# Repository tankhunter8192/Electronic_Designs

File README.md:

# Electronic_Designs
 Collection of Electronic Scemetics and PCB Designs

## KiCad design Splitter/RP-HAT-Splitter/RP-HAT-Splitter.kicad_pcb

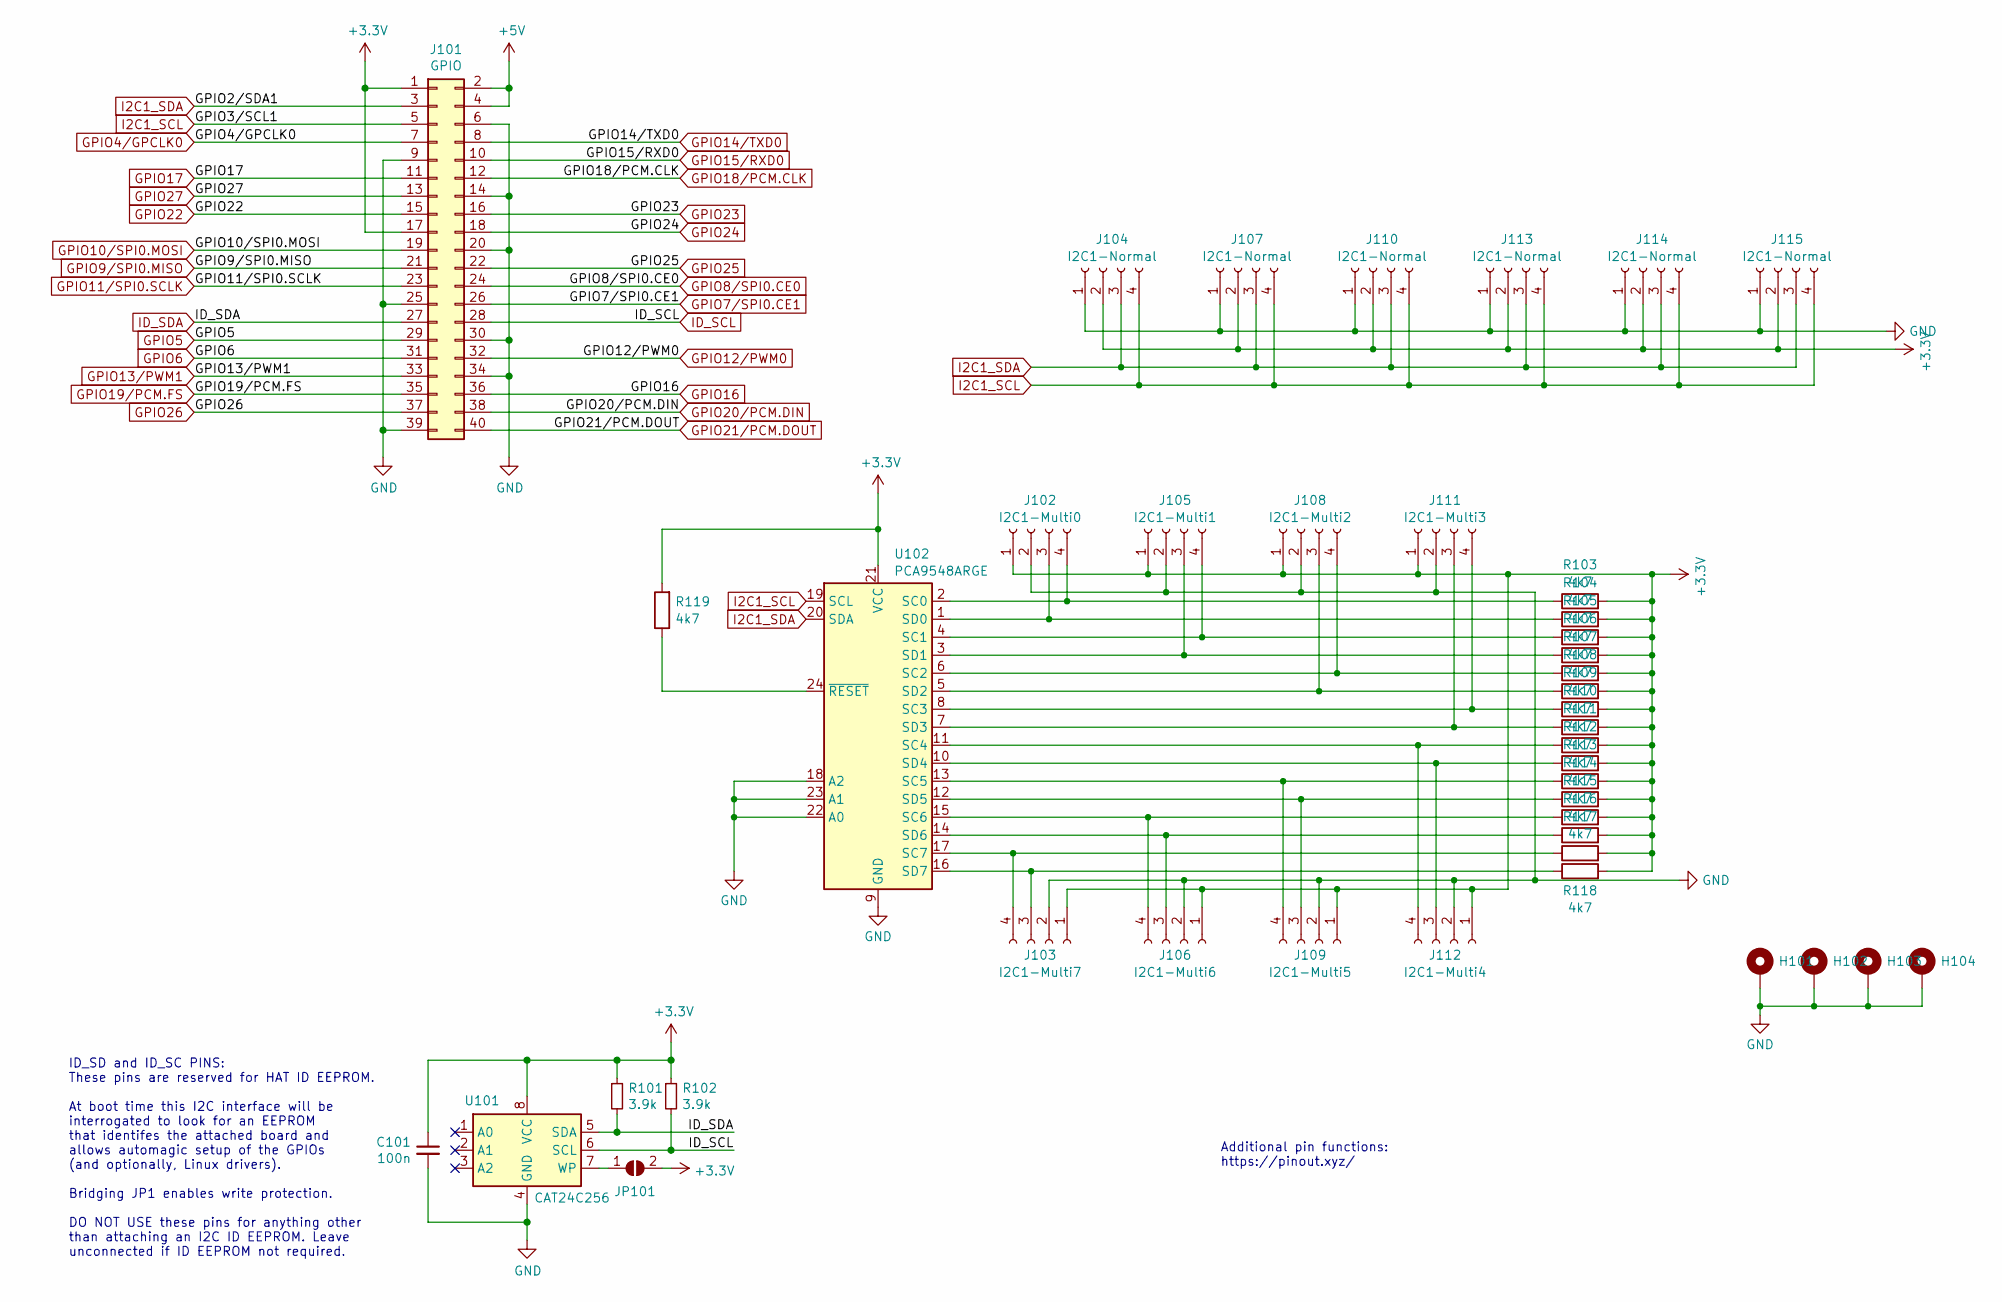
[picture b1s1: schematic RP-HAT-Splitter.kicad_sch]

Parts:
C101: 100n
H101, H102, H103, H104: MountingHole_Pad; MountingHole_3.2mm_M3_DIN965_Pad_TopBottom
J101: GPIO; PinSocket_2x20_P2.54mm_Vertical
J102: I2C1-Multi0; JST_SH_SM04B-SRSS-TB_1x04-1MP_P1.00mm_Horizontal
J103: I2C1-Multi7; JST_SH_SM04B-SRSS-TB_1x04-1MP_P1.00mm_Horizontal
J104, J107, J110, J113, J114, J115: I2C1-Normal; JST_SH_BM04B-SRSS-TB_1x04-1MP_P1.00mm_Vertical
J105: I2C1-Multi1; JST_SH_SM04B-SRSS-TB_1x04-1MP_P1.00mm_Horizontal
J106: I2C1-Multi6; JST_SH_SM04B-SRSS-TB_1x04-1MP_P1.00mm_Horizontal
J108: I2C1-Multi2; JST_SH_SM04B-SRSS-TB_1x04-1MP_P1.00mm_Horizontal
J109: I2C1-Multi5; JST_SH_SM04B-SRSS-TB_1x04-1MP_P1.00mm_Horizontal
J111: I2C1-Multi3; JST_SH_SM04B-SRSS-TB_1x04-1MP_P1.00mm_Horizontal
J112: I2C1-Multi4; JST_SH_SM04B-SRSS-TB_1x04-1MP_P1.00mm_Horizontal
JP101: ID_WP; SolderJumper-3_P2.0mm_Open_TrianglePad1.0x1.5mm_NumberLabels
R101, R102: 3.9k; R_0612_1632Metric_Pad1.18x3.40mm_HandSolder
R103, R104, R105, R106, R107, R108, R109, R110, R111, R112, R113, R114, R115, R116, R117, R118, R119: 4k7; R_1206_3216Metric_Pad1.30x1.75mm_HandSolder
U101: CAT24C256; SOIC127P600X175-8M
U102: PCA9548ARGE; Texas_RGE0024C_EP2.1x2.1mm

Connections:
+3V3: C101.1, J101.1, J101.17, J102.1, J103.1, J104.2, J105.1, J106.1, J107.2, J108.1, J109.1, J110.2, J111.1, J112.1, J113.2, J114.2, J115.2, JP101.2 (B), R101.1, R102.1, R103.2, R104.2, R105.2, R106.2, R107.2, R108.2, R109.2, R110.2, R111.2, R112.2, R113.2, R114.2, R115.2, R116.2, R117.2, R118.2, R119.2, U101.8 (VCC), U102.21 (VCC)
+5V: J101.2, J101.4
GND: C101.2, H101.1, H102.1, H103.1, H104.1, J101.6, J101.9, J101.14, J101.20, J101.25, J101.30, J101.34, J101.39, J102.2, J103.2, J103.MP, J104.1, J104.MP, J105.2, J105.MP, J106.2, J106.MP, J107.1, J107.MP, J108.2, J108.MP, J109.2, J109.MP, J110.1, J110.MP, J111.2, J111.MP, J112.2, J112.MP, J113.1, J113.MP, J114.1, J114.MP, J115.1, J115.MP, U101.4 (GND), U102.9 (GND), U102.18 (A2), U102.22 (A0), U102.23 (A1)
GPIO4/GPCLK0: J101.7
GPIO5: J101.29
GPIO6: J101.31
GPIO7/SPI0.CE1: J101.26
GPIO8/SPI0.CE0: J101.24
GPIO9/SPI0.MISO: J101.21
GPIO10/SPI0.MOSI: J101.19
GPIO11/SPI0.SCLK: J101.23
GPIO12/PWM0: J101.32
GPIO13/PWM1: J101.33
GPIO14/TXD0: J101.8
GPIO15/RXD0: J101.10
GPIO16: J101.36
GPIO17: J101.11
GPIO18/PCM.CLK: J101.12
GPIO19/PCM.FS: J101.35
GPIO20/PCM.DIN: J101.38
GPIO21/PCM.DOUT: J101.40
GPIO22: J101.15
GPIO23: J101.16
GPIO24: J101.18
GPIO25: J101.22
GPIO26: J101.37
GPIO27: J101.13
I2C1_SCL: J101.5, J104.4, J107.4, J110.4, J113.4, J114.4, J115.4, U102.19 (SCL)
I2C1_SDA: J101.3, J104.3, J107.3, J110.3, J113.3, J114.3, J115.3, U102.20 (SDA)
ID_SCL: J101.28, R102.2, U101.6 (SCL)
ID_SDA: J101.27, R101.2, U101.5 (SDA)
unnamed: J102.3, R104.1, U102.1 (SD0)
unnamed: J102.4, R103.1, U102.2 (SC0)
unnamed: J103.3, R118.1, U102.16 (SD7)
unnamed: J103.4, R117.1, U102.17 (SC7)
unnamed: J105.3, R106.1, U102.3 (SD1)
unnamed: J105.4, R105.1, U102.4 (SC1)
unnamed: J106.3, R116.1, U102.14 (SD6)
unnamed: J106.4, R115.1, U102.15 (SC6)
unnamed: J108.3, R108.1, U102.5 (SD2)
unnamed: J108.4, R107.1, U102.6 (SC2)
unnamed: J109.3, R114.1, U102.12 (SD5)
unnamed: J109.4, R113.1, U102.13 (SC5)
unnamed: J111.3, R110.1, U102.7 (SD3)
unnamed: J111.4, R109.1, U102.8 (SC3)
unnamed: J112.3, R112.1, U102.10 (SD4)
unnamed: J112.4, R111.1, U102.11 (SC4)
unnamed: JP101.1 (A), U101.7 (WP)
unnamed: R119.1, U102.24 (~RESET)

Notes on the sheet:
Additional pin functions: https://pinout.xyz/
ID_SD and ID_SC PINS: These pins are reserved for HAT ID EEPROM. At boot time this I2C interface will be interrogated to look for an EEPROM that identifes the attached board and allows automagic setup of the GPIOs (and optionally, Linux drivers). Bridging JP1 enables write protection. DO NOT USE th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

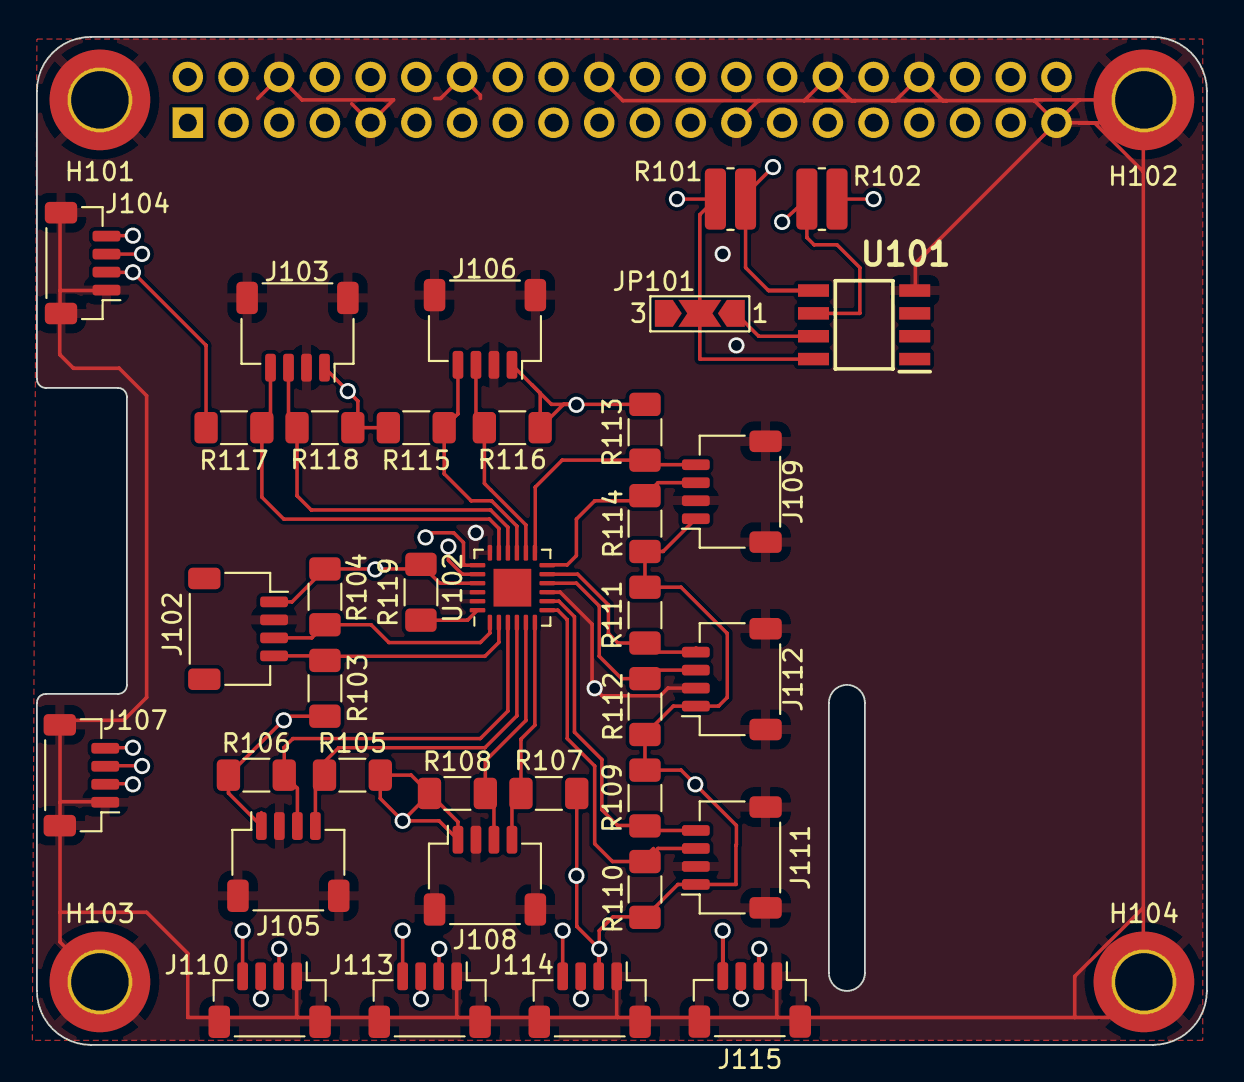
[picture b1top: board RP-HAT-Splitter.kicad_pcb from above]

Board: 4 copper layers, 65.0 x 56.0 mm, 41 parts (1 on the bottom side), 25 nets.

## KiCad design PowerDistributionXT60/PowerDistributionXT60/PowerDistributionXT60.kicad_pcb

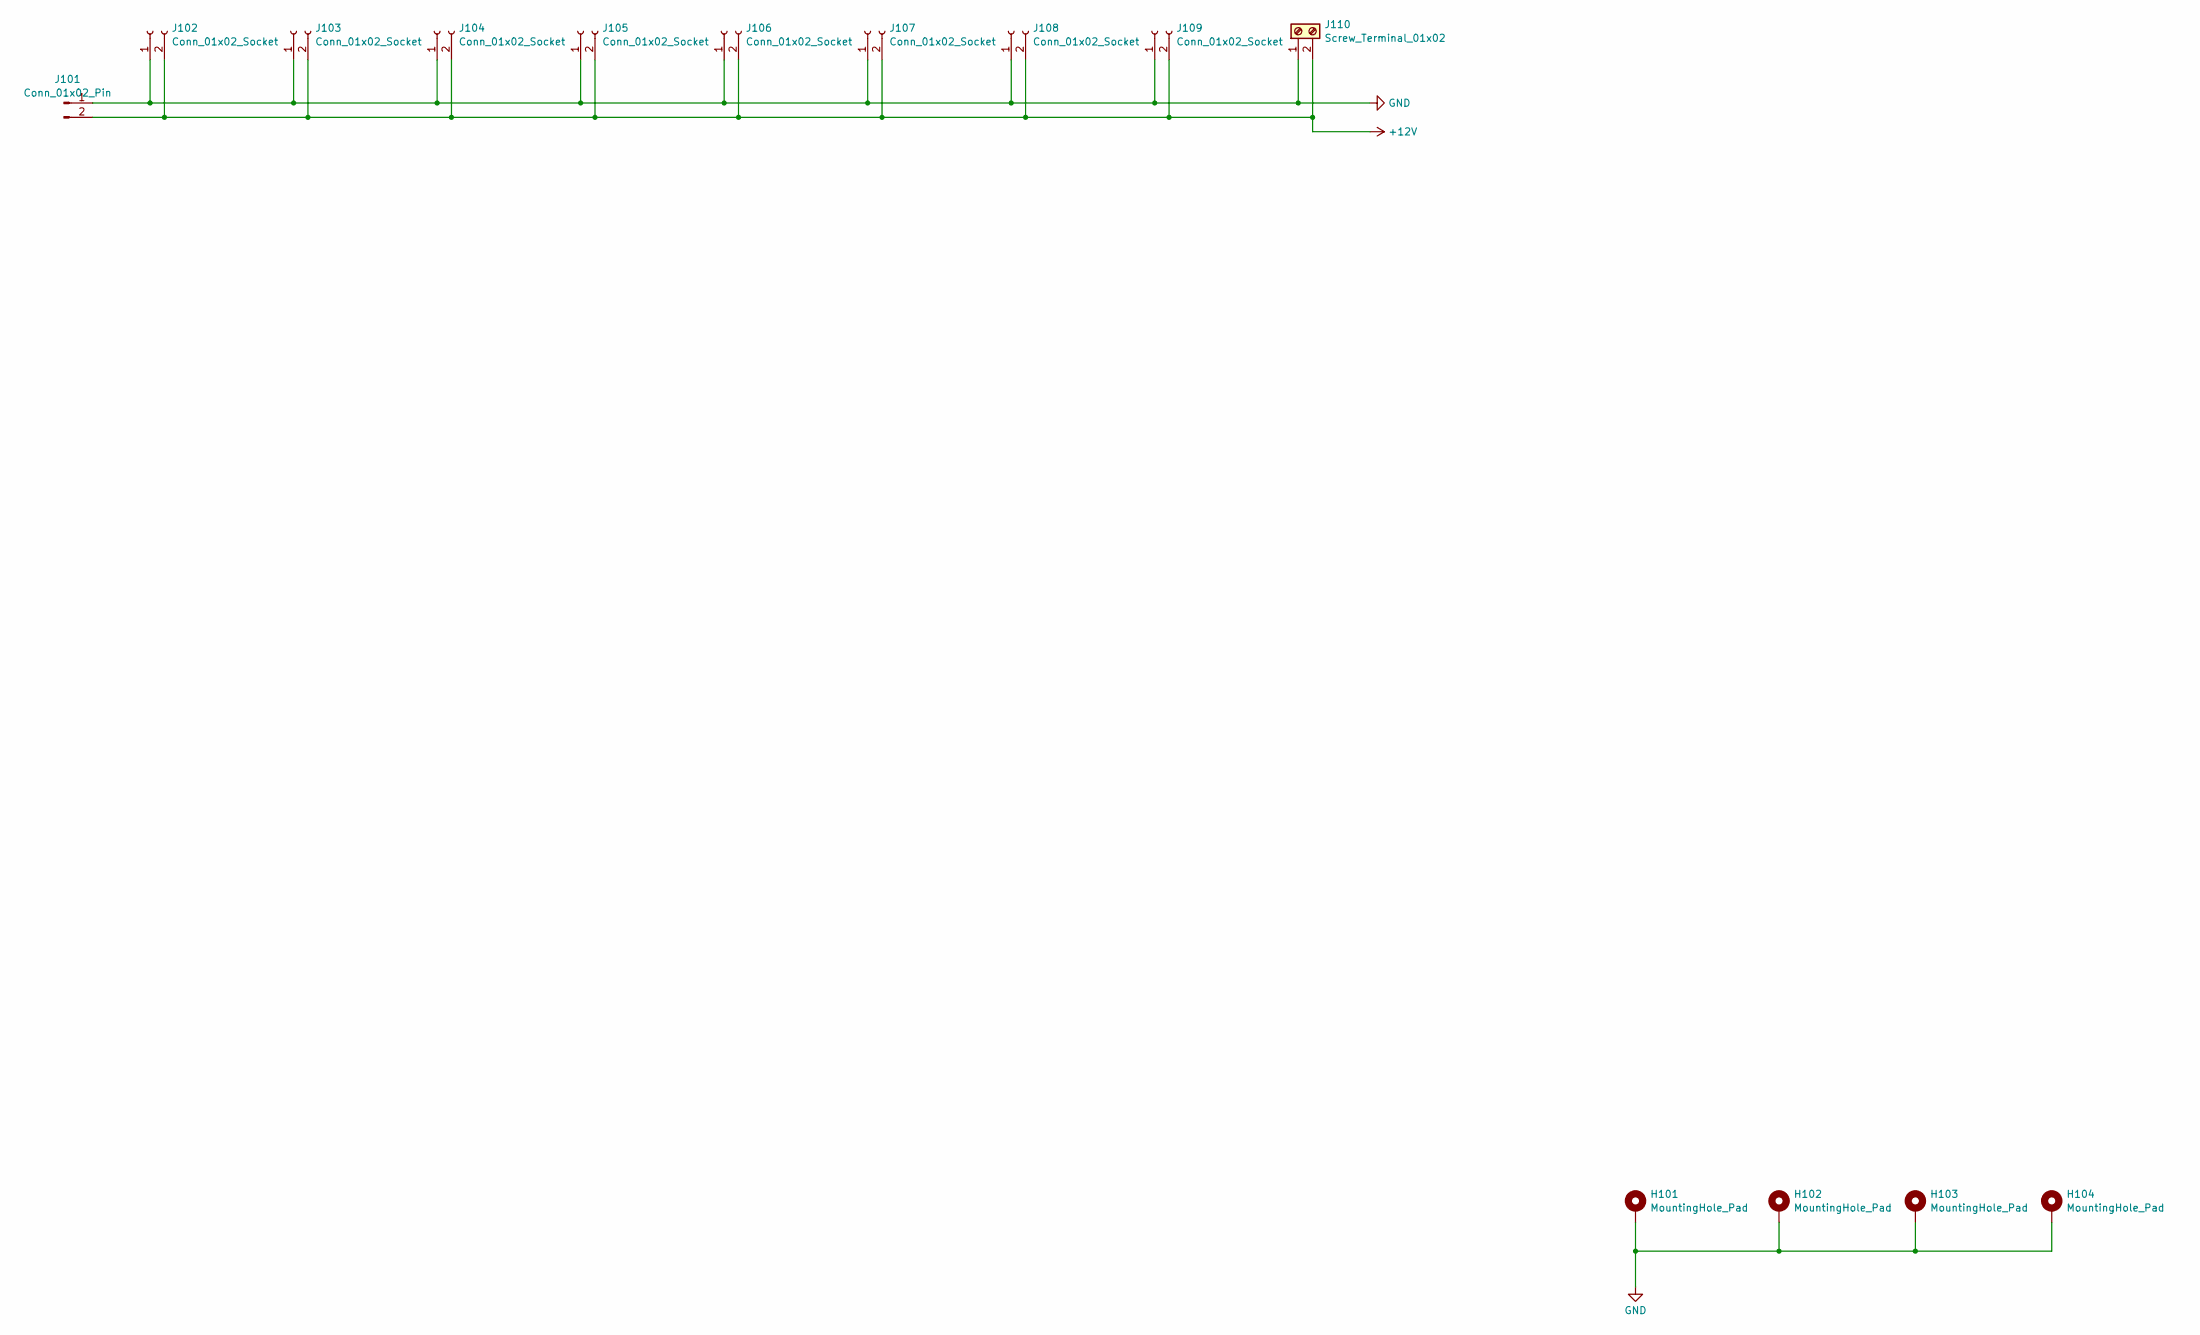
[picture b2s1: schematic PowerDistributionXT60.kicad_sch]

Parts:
H101, H102, H103, H104: MountingHole_Pad; MountingHole_5.3mm_M5_ISO14580_Pad_TopBottom
J101: Conn_01x02_Pin; AMASS_XT60-M_1x02_P7.20mm_Vertical
J102, J103, J104, J105, J106, J107, J108, J109: Conn_01x02_Socket; AMASS_XT60-M_1x02_P7.20mm_Vertical
J110: Screw_Terminal_01x02; TerminalBlock_Phoenix_MKDS-1,5-2-5.08_1x02_P5.08mm_Horizont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

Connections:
+12V: J101.2, J102.2, J103.2, J104.2, J105.2, J106.2, J107.2, J108.2, J109.2, J110.2
GND: H101.1, H102.1, H103.1, H104.1, J101.1, J102.1, J103.1, J104.1, J105.1, J106.1, J107.1, J108.1, J109.1, J110.1

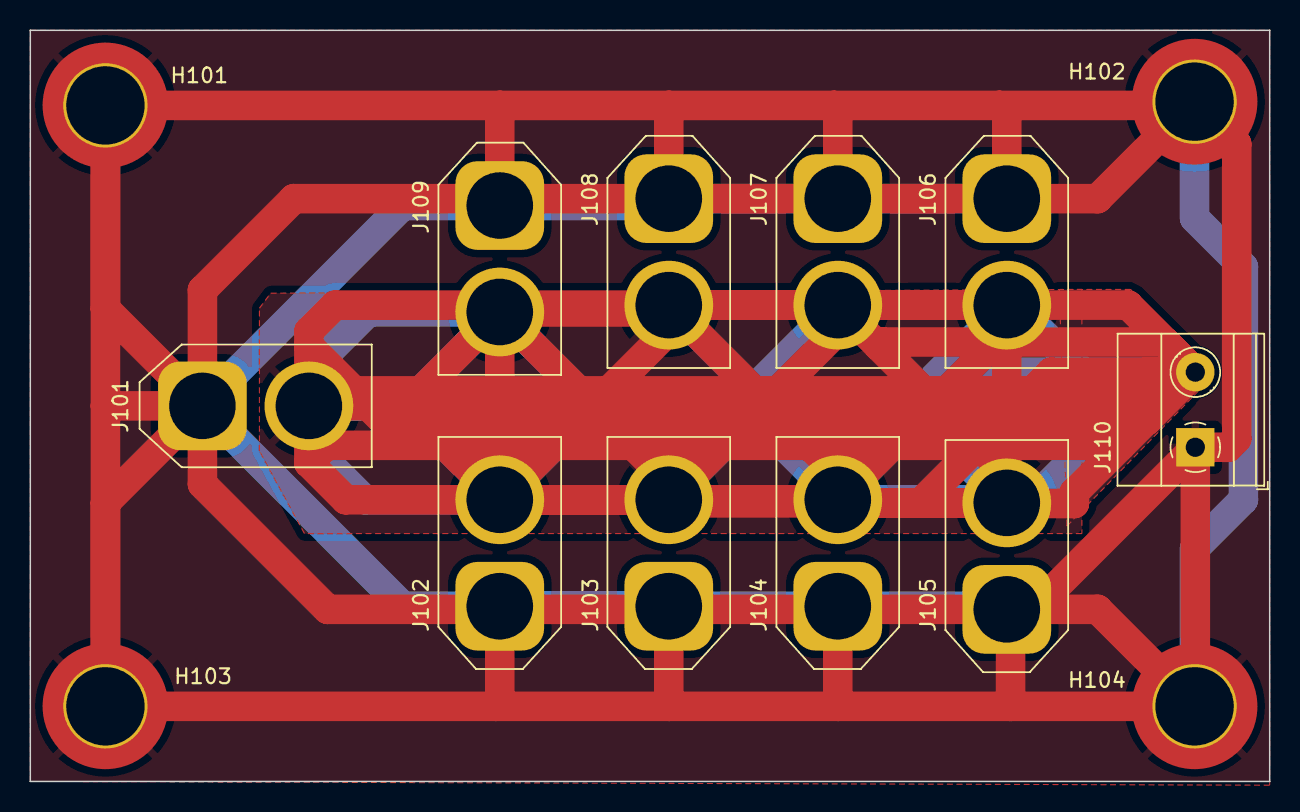
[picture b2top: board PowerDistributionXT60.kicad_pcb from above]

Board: 2 copper layers, 83.8 x 50.8 mm, 14 parts (0 on the bottom side), 2 nets.

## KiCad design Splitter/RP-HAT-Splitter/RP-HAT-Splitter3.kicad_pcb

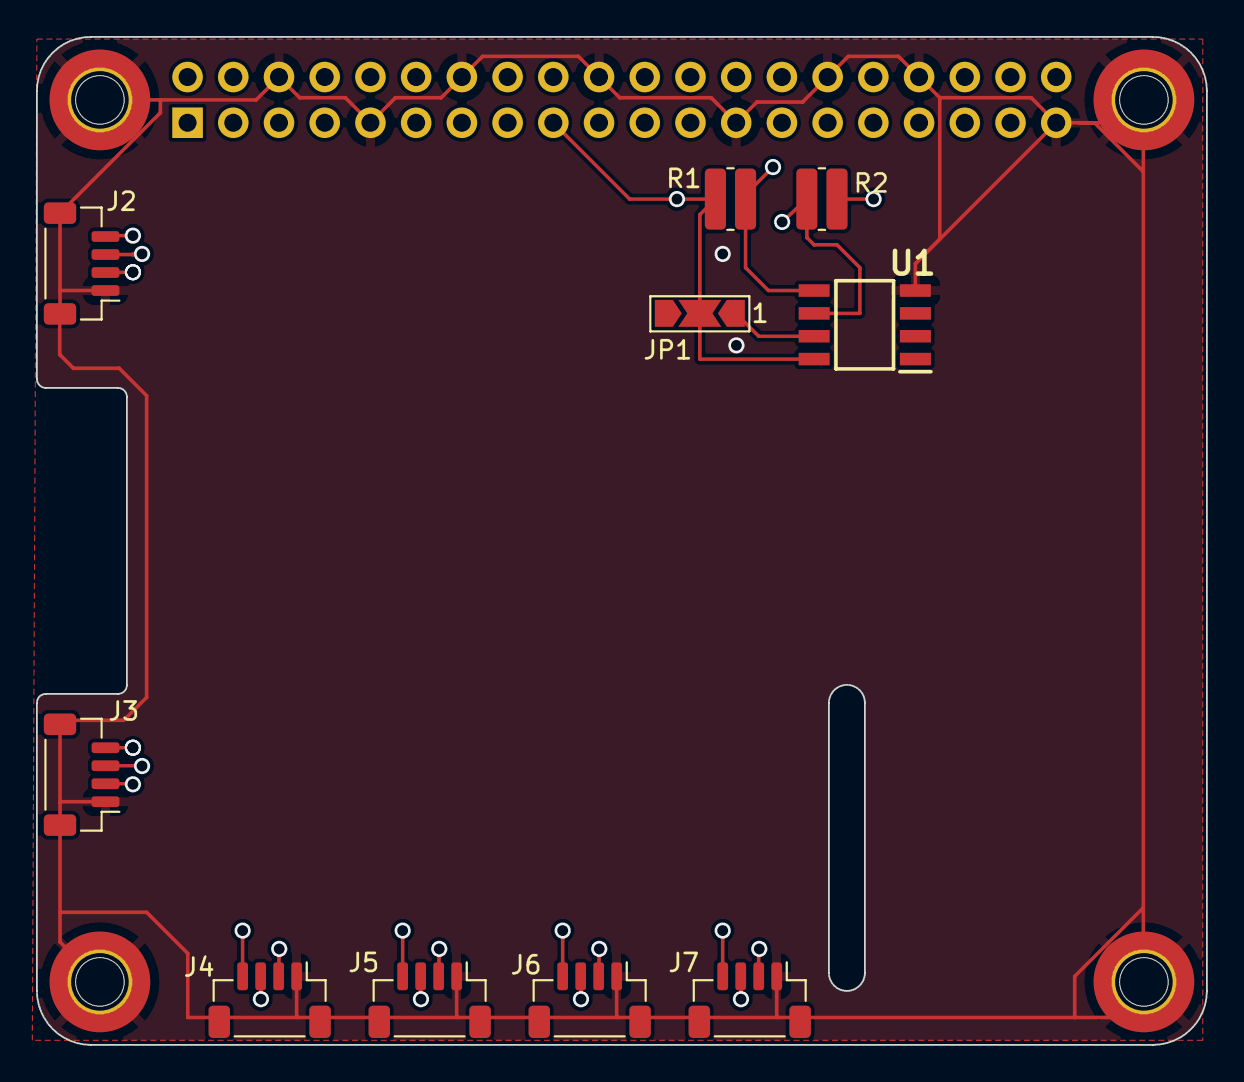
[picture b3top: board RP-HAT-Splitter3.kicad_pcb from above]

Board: 4 copper layers, 65.0 x 56.0 mm, 19 parts (1 on the bottom side), 8 nets.

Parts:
H1, H2, H3, H4: MountingHole_Pad; MountingHole_3.2mm_M3_DIN965_Pad_TopBottom
J1: GPIO; PinSocket_2x20_P2.54mm_Vertical
J2, J3, J4, J5, J6, J7: Conn_01x04_Socket; JST_SH_BM04B-SRSS-TB_1x04-1MP_P1.00mm_Vertical
JP1: ID_WP; SolderJumper-3_P2.0mm_Open_TrianglePad1.0x1.5mm_NumberLabels
MH1, MH2, MH3, MH4: MountingHole_2.7mm_M2.5
R1, R2: 3.9k; R_0612_1632Metric_Pad1.18x3.40mm_HandSolder
U1: CAT24C256; SOIC127P600X175-8M

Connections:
+3V3: J1.1, J1.17, J2.2, J3.2, J4.2, J5.2, J6.2, J7.2, JP1.2 (B), R1.1, R2.1, U1.8 (VCC)
+5V: J1.2, J1.4
GND: H1.1, H2.1, H3.1, H4.1, J1.6, J1.9, J1.14, J1.20, J1.25, J1.30, J1.34, J1.39, J2.1, J3.1, J4.1, J5.1, J6.1, J7.1, U1.4 (GND)
I2C1_SCL: J1.5, J2.4, J3.4, J4.4, J5.4, J6.4, J7.4
I2C1_SDA: J1.3, J2.3, J3.3, J4.3, J5.3, J6.3, J7.3
ID_SCL: J1.28, R2.2, U1.6 (SCL)
ID_SDA: J1.27, R1.2, U1.5 (SDA)
unnamed: JP1.1 (A), U1.7 (WP)

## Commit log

2021-08-06 JetsonNanoPowerHat V1 init
    Jetson Nano Power Hat Project created
2023-09-26 adding of HAT Splitter V001
2023-09-26 remove of lock file
2023-09-26 update of gitignore
